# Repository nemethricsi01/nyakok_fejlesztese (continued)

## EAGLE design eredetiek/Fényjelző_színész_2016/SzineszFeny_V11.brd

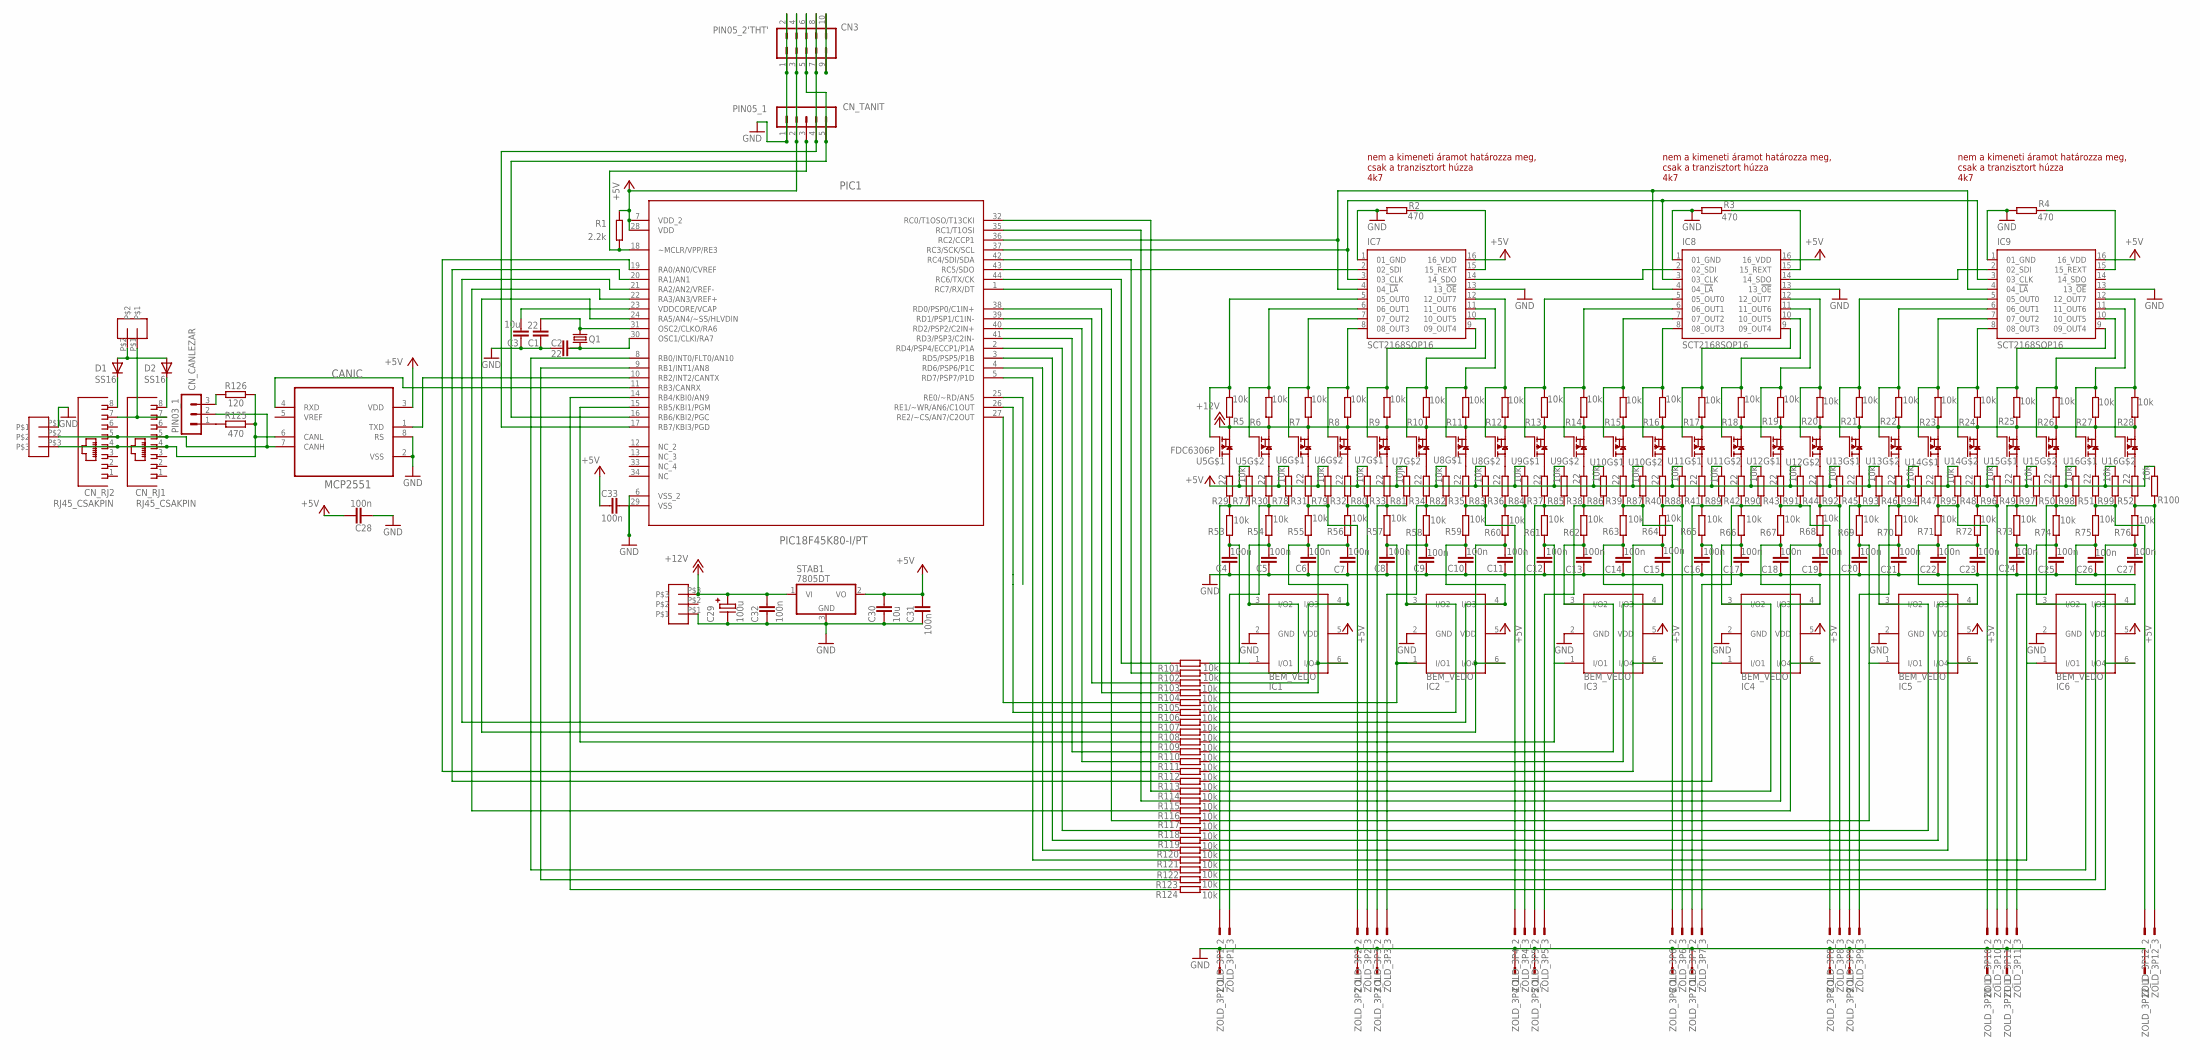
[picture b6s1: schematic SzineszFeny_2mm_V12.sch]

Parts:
C1, C2: 22; R0805
C3, C30: 10u; R0805
C4, C5, C6, C7, C8, C9, C10, C11, C12, C13, C14, C15, C16, C17, C18, C19, C20, C21, C22, C23, C24, C25, C26, C27, C28, C31, C32, C33: 100n; R0805
C29: 100u; C_EL1RASZT07
CANIC: MCP2551; DIP254P762X432-8
CN3: PIN05_2'THT'; PIN05_2
CN_CANLEZAR: PIN03_1
CN_RJ1, CN_RJ2: RJ45_CSAKPIN
CN_TANIT: PIN05_1
D1, D2: SS16; DO214AC
IC1, IC2, IC3, IC4, IC5, IC6: BEM_VEDO; TSOP-6
IC7, IC8, IC9: SCT2168SOP16; SO16
PIC1: PIC18F45K80-I/PT; QFP80P1200X1200X120-44N
Q1: XTAL_2QS; XTAL_QS
R1: 2.2k; R0805@1
R2, R3, R4, R125: 470; R0805@1
R5, R6, R7, R8, R9, R10, R11, R12, R13, R14, R15, R16, R17, R18, R19, R20, R21, R22, R23, R24, R25, R26, R27, R28, R53, R54, R55, R56, R57, R58, R59, R60, R61, R62, R63, R64, R65, R66, R67, R68, R69, R70, R71, R72, R73, R74, R75, R76, R77, R78, R79, R80, R82, R83, R84, R85, R86, R87, R88, R89, R90, R91, R92, R93, R94, R95, R96, R97, R98, R99, R100, R101, R102, R103, R104, R105, R106, R107, R108, R109, R110, R111, R112, R113, R114, R115, R116, R117, R118, R119, R120, R121, R122, R123, R124: 10k; R0805@1
R29, R30, R31, R32, R33, R34, R35, R36, R37, R38, R39, R40, R41, R42, R43, R44, R45, R46, R47, R48, R49, R50, R51, R52: 22; R0805@1
R81: 10jk; R0805@1
R126: 120; R0805@1
STAB1: 7805DT; TO252
U5, U16: FDC6306P; SOT26
U6, U7, U8, U9, U10, U11, U12, U13, U14, U15: AP2625GY-HF-3SOT26; SOT26
U$1, U$20: FEHER_TUS_3
U$21: FEHER_TUS_2ALLO; FEHER_TUS_2
ZOLD_3P1, ZOLD_3P2, ZOLD_3P3, ZOLD_3P4, ZOLD_3P5, ZOLD_3P6, ZOLD_3P7, ZOLD_3P8, ZOLD_3P9, ZOLD_3P10, ZOLD_3P11, ZOLD_3P12: ZOLD_KICSI_3P

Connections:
+5V: C28.1, C30.1, C31.1, C33.2, CANIC.3 (VDD), CN3.3, CN3.4, CN_TANIT.2, IC1.5 (VDD), IC2.5 (VDD), IC3.5 (VDD), IC4.5 (VDD), IC5.5 (VDD), IC6.5 (VDD), IC7.16 (16_VDD), IC8.16 (16_VDD), IC9.16 (16_VDD), PIC1.7 (VDD_2), PIC1.28 (VDD), R1.2 (E), R77.1 (A), R78.1 (A), R79.1 (A), R80.1 (A), R81.1 (A), R82.1 (A), R83.1 (A), R84.1 (A), R85.1 (A), R86.1 (A), R87.1 (A), R88.1 (A), R89.1 (A), R90.1 (A), R91.1 (A), R92.1 (A), R93.1 (A), R94.1 (A), R95.1 (A), R96.1 (A), R97.1 (A), R98.1 (A), R99.1 (A), R100.1 (A), STAB1.2 (VO)
+12V: C29.P+, C32.1, R5.1 (A), R6.1 (A), R7.1 (A), R8.1 (A), R9.1 (A), R10.1 (A), R11.1 (A), R12.1 (A), R13.1 (A), R14.1 (A), R15.1 (A), R16.1 (A), R17.1 (A), R18.1 (A), R19.1 (A), R20.1 (A), R21.1 (A), R22.1 (A), R23.1 (A), R24.1 (A), R25.1 (A), R26.1 (A), R27.1 (A), R28.1 (A), STAB1.1 (VI), U5.P$2 (S), U5.P$5 (S), U6.P$2 (S), U6.P$5 (S), U7.P$2 (S), U7.P$5 (S), U8.P$2 (S), U8.P$5 (S), U9.P$2 (S), U9.P$5 (S), U10.P$2 (S), U10.P$5 (S), U11.P$2 (S), U11.P$5 (S), U12.P$2 (S), U12.P$5 (S), U13.P$2 (S), U13.P$5 (S), U14.P$2 (S), U14.P$5 (S), U15.P$2 (S), U15.P$5 (S), U16.P$2 (S), U16.P$5 (S), U$20.P$3
GND: C1.2, C2.2, C3.2, C4.2, C5.2, C6.2, C7.2, C8.2, C9.2, C10.2, C11.2, C12.2, C13.2, C14.2, C15.2, C16.2, C17.2, C18.2, C19.2, C20.2, C21.2, C22.2, C23.2, C24.2, C25.2, C26.2, C27.2, C28.2, C29.P-, C30.2, C31.2, C32.2, C33.1, CANIC.2 (VSS), CANIC.8 (RS), CN3.1, CN3.2, CN_TANIT.1, IC1.2 (GND), IC2.2 (GND), IC3.2 (GND), IC4.2 (GND), IC5.2 (GND), IC6.2 (GND), IC7.1 (01_GND), IC7.13 (13_!OE!), IC8.1 (01_GND), IC8.13 (13_!OE!), IC9.1 (01_GND), IC9.13 (13_!OE!), PIC1.6 (VSS_2), PIC1.29 (VSS), R2.1 (A), R3.1 (A), R4.1 (A), STAB1.3 (GND), U$1.P$1, U$20.P$1, ZOLD_3P1.1, ZOLD_3P2.1, ZOLD_3P3.1, ZOLD_3P4.1, ZOLD_3P5.1, ZOLD_3P6.1, ZOLD_3P7.1, ZOLD_3P8.1, ZOLD_3P9.1, ZOLD_3P10.1, ZOLD_3P11.1, ZOLD_3P12.1
unnamed: C3.1, PIC1.23 (VDDCORE/VCAP)
unnamed: CN_TANIT.3, PIC1.18 (~MCLR/VPP/RE3), R1.1 (A)
unnamed: CN3.7, CN3.8, CN_TANIT.4, PIC1.17 (RB7/KBI3/PGD)
unnamed: IC7.14 (14_SDO), IC8.2 (02_SDI)
unnamed: C1.1, PIC1.31 (OSC2/CLKO/RA6), Q1.2
unnamed: C2.1, PIC1.30 (OSC1/CLKI/RA7), Q1.1
unnamed: PIC1.19 (RA0/AN0/CVREF), R112.1 (A)
unnamed: PIC1.20 (RA1/AN1), R113.1 (A)
unnamed: PIC1.22 (RA3/AN3/VREF+), R116.1 (A)
unnamed: PIC1.21 (RA2/AN2/VREF-), R107.1 (A)
unnamed: PIC1.24 (RA5/AN4/~SS/HLVDIN), R108.1 (A)
unnamed: IC8.7 (07_OUT2), R15.2 (E), U10.P$1 (G)
unnamed: IC7.6 (06_OUT1), R6.2 (E), U5.P$3 (G)
unnamed: IC9.5 (05_OUT0), R21.2 (E), U13.P$1 (G)
unnamed: IC8.15 (15_REXT), R3.2 (E)
unnamed: IC8.5 (05_OUT0), R13.2 (E), U9.P$1 (G)
unnamed: IC7.3 (03_CLK), IC8.3 (03_CLK), IC9.3 (03_CLK), PIC1.37 (RC3/SCK/SCL)
unnamed: IC7.4 (04_!LA!), IC8.4 (04_!LA!), IC9.4 (04_!LA!), PIC1.36 (RC2/CCP1)
unnamed: IC9.6 (06_OUT1), R22.2 (E), U13.P$3 (G)
unnamed: IC9.7 (07_OUT2), R23.2 (E), U14.P$1 (G)
unnamed: IC7.8 (08_OUT3), R8.2 (E), U6.P$3 (G)
unnamed: IC9.15 (15_REXT), R4.2 (E)
unnamed: CN_CANLEZAR.1, R125.2 (E)
unnamed: IC9.8 (08_OUT3), R24.2 (E), U14.P$3 (G)
unnamed: IC8.6 (06_OUT1), R14.2 (E), U9.P$3 (G)
unnamed: IC7.5 (05_OUT0), R5.2 (E), U5.P$1 (G)
unnamed: IC7.7 (07_OUT2), R7.2 (E), U6.P$1 (G)
unnamed: IC8.8 (08_OUT3), R16.2 (E), U10.P$3 (G)
unnamed: IC9.9 (09_OUT4), R25.2 (E), U15.P$1 (G)
unnamed: IC8.9 (09_OUT4), R17.2 (E), U11.P$1 (G)
unnamed: IC9.10 (10_OUT5), R26.2 (E), U15.P$3 (G)
unnamed: IC8.10 (10_OUT5), R18.2 (E), U11.P$3 (G)
unnamed: IC7.9 (09_OUT4), R9.2 (E), U7.P$1 (G)
unnamed: IC9.11 (11_OUT6), R27.2 (E), U16.P$1 (G)
unnamed: IC8.11 (11_OUT6), R19.2 (E), U12.P$1 (G)
unnamed: IC8.12 (12_OUT7), R20.2 (E), U12.P$3 (G)
unnamed: IC7.10 (10_OUT5), R10.2 (E), U7.P$3 (G)
unnamed: IC7.11 (11_OUT6), R11.2 (E), U8.P$1 (G)
unnamed: IC7.12 (12_OUT7), R12.2 (E), U8.P$3 (G)
unnamed: IC9.12 (12_OUT7), R28.2 (E), U16.P$3 (G)
unnamed: R29.2 (E), U5.P$6 (D)
unnamed: R30.2 (E), U5.P$4 (D)
unnamed: R31.2 (E), U6.P$6 (D)
unnamed: R32.2 (E), U6.P$4 (D)
unnamed: R33.2 (E), U7.P$6 (D)
unnamed: R34.2 (E), U7.P$4 (D)
unnamed: R35.2 (E), U8.P$6 (D)
unnamed: R36.2 (E), U8.P$4 (D)
unnamed: R37.2 (E), U9.P$6 (D)
unnamed: R38.2 (E), U9.P$4 (D)
unnamed: R39.2 (E), U10.P$6 (D)
unnamed: R40.2 (E), U10.P$4 (D)
unnamed: R41.2 (E), U11.P$6 (D)
unnamed: R42.2 (E), U11.P$4 (D)
unnamed: R43.2 (E), U12.P$6 (D)
unnamed: R44.2 (E), U12.P$4 (D)
unnamed: R45.2 (E), U13.P$6 (D)
unnamed: R46.2 (E), U13.P$4 (D)
unnamed: R47.2 (E), U14.P$6 (D)
unnamed: R48.2 (E), U14.P$4 (D)
unnamed: R49.2 (E), U15.P$6 (D)
unnamed: R50.2 (E), U15.P$4 (D)
unnamed: IC7.2 (02_SDI), PIC1.43 (RC5/SDO)
unnamed: R51.2 (E), U16.P$6 (D)
unnamed: R52.2 (E), U16.P$4 (D)
unnamed: CN3.5, CN3.6, CN_TANIT.5, PIC1.16 (RB6/KBI2/PGC)
unnamed: PIC1.27 (RE2/~CS/AN7/C2OUT), R105.1 (A)
unnamed: R31.1 (A), R55.2 (E), R79.2 (E), ZOLD_3P2.2
unnamed: R32.1 (A), R56.2 (E), R80.2 (E), ZOLD_3P2.3
unnamed: R33.1 (A), R57.2 (E), R81.2 (E), ZOLD_3P3.2
unnamed: PIC1.26 (RE1/~WR/AN6/C1OUT), R106.1 (A)
unnamed: R35.1 (A), R59.2 (E), R83.2 (E), ZOLD_3P4.2
unnamed: R36.1 (A), R60.2 (E), R84.2 (E), ZOLD_3P4.3
unnamed: R37.1 (A), R61.2 (E), R85.2 (E), ZOLD_3P5.2
unnamed: R38.1 (A), R62.2 (E), R86.2 (E), ZOLD_3P5.3
unnamed: R39.1 (A), R63.2 (E), R87.2 (E), ZOLD_3P6.2
unnamed: R40.1 (A), R64.2 (E), R88.2 (E), ZOLD_3P6.3
unnamed: R41.1 (A), R65.2 (E), R89.2 (E), ZOLD_3P7.2
unnamed: R42.1 (A), R66.2 (E), R90.2 (E), ZOLD_3P7.3
unnamed: R43.1 (A), R67.2 (E), R91.2 (E), ZOLD_3P8.2
unnamed: R44.1 (A), R68.2 (E), R92.2 (E), ZOLD_3P8.3
unnamed: R45.1 (A), R69.2 (E), R93.2 (E), ZOLD_3P9.2
unnamed: R46.1 (A), R70.2 (E), R94.2 (E), ZOLD_3P9.3
unnamed: R47.1 (A), R71.2 (E), R95.2 (E), ZOLD_3P10.2
unnamed: R48.1 (A), R72.2 (E), R96.2 (E), ZOLD_3P10.3
unnamed: R49.1 (A), R73.2 (E), R97.2 (E), ZOLD_3P11.2
unnamed: IC7.15 (15_REXT), R2.2 (E)
unnamed: R50.1 (A), R74.2 (E), R98.2 (E), ZOLD_3P11.3
unnamed: R51.1 (A), R75.2 (E), R99.2 (E), ZOLD_3P12.2
unnamed: R52.1 (A), R76.2 (E), R100.2 (E), ZOLD_3P12.3
unnamed: C4.1, IC1.1 (I/O1), R53.1 (A), R101.2 (E)
unnamed: R29.1 (A), R53.2 (E), R77.2 (E), ZOLD_3P1.2
unnamed: C5.1, IC1.3 (I/O2), R54.1 (A), R102.2 (E)
unnamed: C6.1, IC1.4 (I/O3), R55.1 (A), R103.2 (E)
unnamed: C7.1, IC1.6 (I/O4), R56.1 (A), R104.2 (E)
unnamed: C11.1, IC2.6 (I/O4), R60.1 (A), R108.2 (E)
unnamed: R34.1 (A), R58.2 (E), R82.2 (E), ZOLD_3P3.3
unnamed: C8.1, IC2.1 (I/O1), R57.1 (A), R105.2 (E)
unnamed: CANIC.6 (CANL), CN_RJ1.4, CN_RJ2.4, R125.1 (A), R126.2 (E), U$1.P$3
unnamed: C12.1, IC3.1 (I/O1), R61.1 (A), R109.2 (E)
unnamed: C13.1, IC3.3 (I/O2), R62.1 (A), R110.2 (E)
unnamed: C17.1, IC4.3 (I/O2), R66.1 (A), R114.2 (E)
unnamed: C15.1, IC3.6 (I/O4), R64.1 (A), R112.2 (E)
unnamed: C16.1, IC4.1 (I/O1), R65.1 (A), R113.2 (E)
unnamed: R30.1 (A), R54.2 (E), R78.2 (E), ZOLD_3P1.3
unnamed: C18.1, IC4.4 (I/O3), R67.1 (A), R115.2 (E)
unnamed: C19.1, IC4.6 (I/O4), R68.1 (A), R116.2 (E)
unnamed: C20.1, IC5.1 (I/O1), R69.1 (A), R117.2 (E)
unnamed: C21.1, IC5.3 (I/O2), R70.1 (A), R118.2 (E)
unnamed: C22.1, IC5.4 (I/O3), R71.1 (A), R119.2 (E)
unnamed: C23.1, IC5.6 (I/O4), R72.1 (A), R120.2 (E)
unnamed: C24.1, IC6.1 (I/O1), R73.1 (A), R121.2 (E)
unnamed: C25.1, IC6.3 (I/O2), R74.1 (A), R122.2 (E)
unnamed: C26.1, IC6.4 (I/O3), R75.1 (A), R123.2 (E)
unnamed: C27.1, IC6.6 (I/O4), R76.1 (A), R124.2 (E)
unnamed: PIC1.5 (RD7/PSP7/P1D), R121.1 (A)
unnamed: PIC1.4 (RD6/PSP6/P1C), R120.1 (A)
unnamed: C14.1, IC3.4 (I/O3), R63.1 (A), R111.2 (E)
unnamed: PIC1.3 (RD5/PSP5/P1B), R119.1 (A)
unnamed: PIC1.2 (RD4/PSP4/ECCP1/P1A), R118.1 (A)
unnamed: PIC1.41 (RD3/PSP3/C2IN-), R110.1 (A)
unnamed: PIC1.40 (RD2/PSP2/C2IN+), R111.1 (A)
unnamed: PIC1.39 (RD1/PSP1/C1IN-), R103.1 (A)
unnamed: PIC1.38 (RD0/PSP0/C1IN+), R104.1 (A)
unnamed: PIC1.1 (RC7/RX/DT), R117.1 (A)
unnamed: PIC1.44 (RC6/TX/CK), R101.1 (A)
unnamed: PIC1.42 (RC4/SDI/SDA), R102.1 (A)
unnamed: PIC1.35 (RC1/T1OSI), R115.1 (A)
unnamed: PIC1.32 (RC0/T1OSO/T13CKI), R114.1 (A)
unnamed: CANIC.7 (CANH), CN_CANLEZAR.2, CN_RJ1.5, CN_RJ2.5, U$1.P$2
unnamed: CANIC.1 (TXD), PIC1.10 (RB2/INT2/CANTX)
unnamed: C10.1, IC2.4 (I/O3), R59.1 (A), R107.2 (E)
unnamed: C9.1, IC2.3 (I/O2), R58.1 (A), R106.2 (E)
unnamed: PIC1.15 (RB5/KBI1/PGM), R109.1 (A)
unnamed: PIC1.14 (RB4/KBI0/AN9), R124.1 (A)
unnamed: CANIC.4 (RXD), PIC1.11 (RB3/CANRX)
unnamed: CN_CANLEZAR.3, R126.1 (A)
unnamed: PIC1.9 (RB1/INT1/AN8), R123.1 (A)
unnamed: PIC1.8 (RB0/INT0/FLT0/AN10), R122.1 (A)
unnamed: CN3.9, CN3.10
unnamed: IC8.14 (14_SDO), IC9.2 (02_SDI)
unnamed: CN_RJ2.8, D1.C
unnamed: CN_RJ1.7, CN_RJ2.7, U$21.P$1
unnamed: D1.A, D2.A, U$21.P$2
unnamed: CN_RJ1.8, D2.C

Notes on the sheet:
nem a kimeneti áramot határozza meg, csak a tranzisztort húzza 4k7

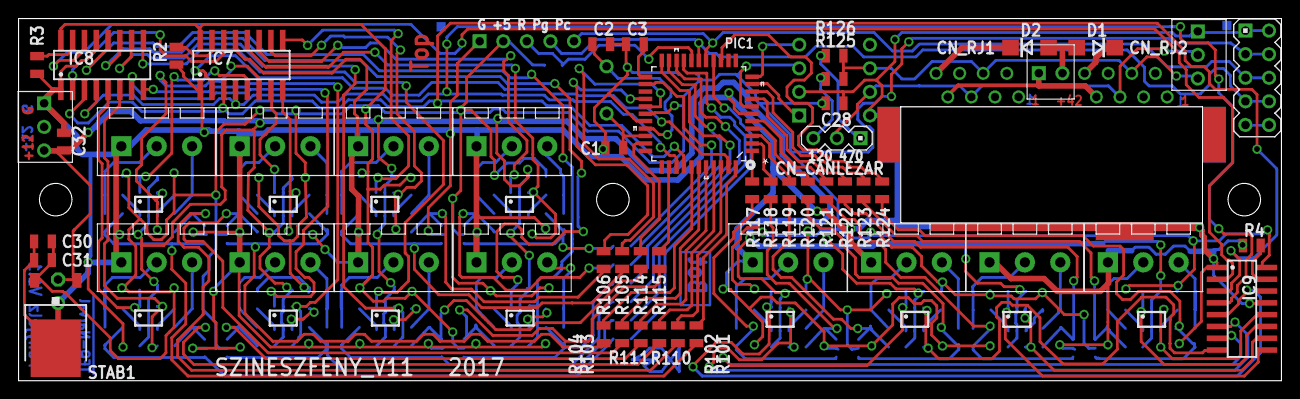
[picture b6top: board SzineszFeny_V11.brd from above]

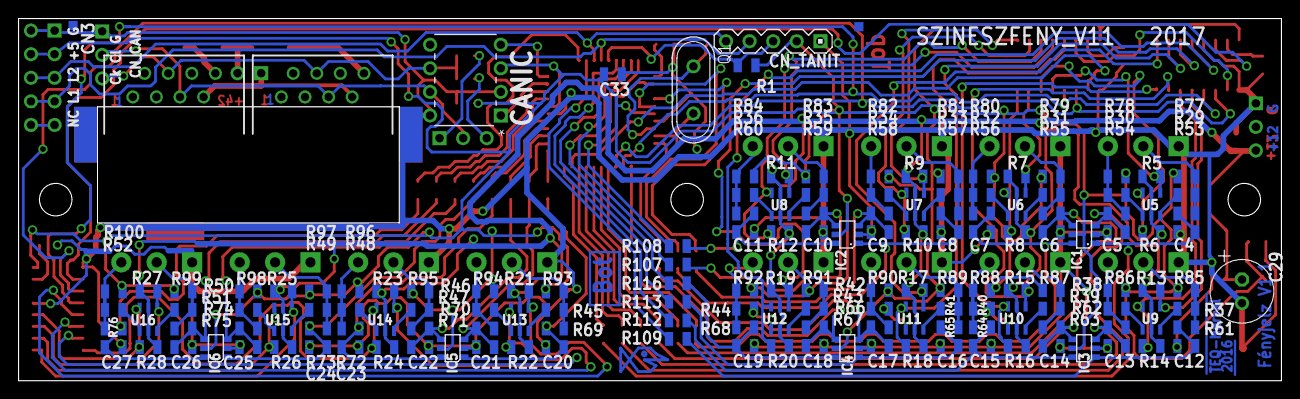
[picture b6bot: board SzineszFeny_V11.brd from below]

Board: 2 copper layers, 136.0 x 39.0 mm, 206 parts (152 on the bottom side), 148 nets.
